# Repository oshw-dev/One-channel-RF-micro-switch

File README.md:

# One-channel-RF-micro-switch
Small one-channel RF microswitch

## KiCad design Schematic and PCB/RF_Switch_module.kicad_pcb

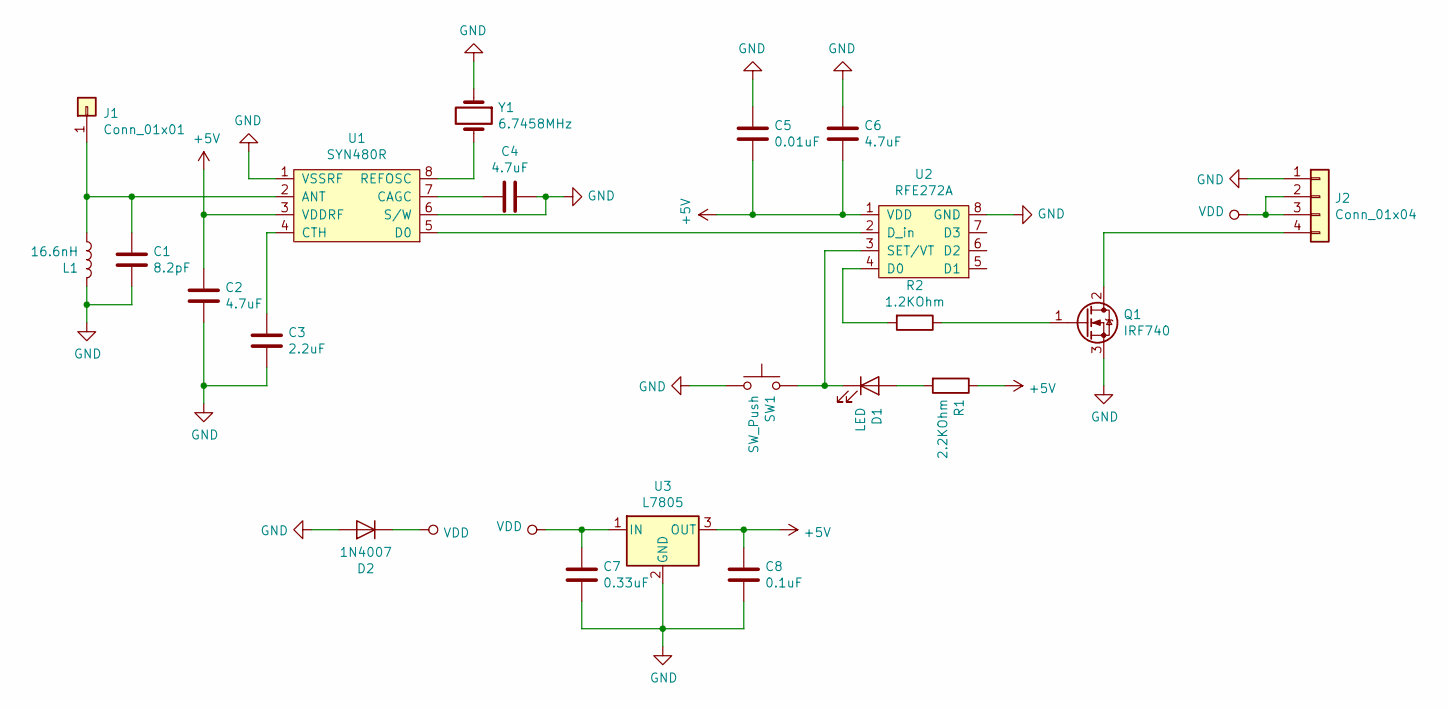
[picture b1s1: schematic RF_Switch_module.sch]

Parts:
C1: 8.2pF; C_0402_1005Metric
C2, C4, C6: 4.7uF; C_0402_1005Metric
C3: 2.2uF; C_0402_1005Metric
C5: 0.01uF; C_0402_1005Metric
C7: 0.33uF; C_0402_1005Metric
C8: 0.1uF; C_0402_1005Metric
D1: LED; LED_0402_1005Metric
D2: 1N4007; D_SOD-123
J1: Conn_01x01; SolderWirePad_1x01_Drill0.8mm
J2: Conn_01x04; PinHeader_1x04_P2.54mm_Horizontal
L1: 16.6nH; L_0402_1005Metric
Q1: IRF740; TO-252-3_TabPin2
R1: 2.2KOhm; R_0402_1005Metric
R2: 1.2KOhm; R_0402_1005Metric
SW1: SW_Push; SW_Push_SPST_NO_Alps_SKRK
U1: SYN480R; SO-8_3.9x4.9mm_P1.27mm
U2: RFE272A; SO-8_3.9x4.9mm_P1.27mm
U3: L7805; SOT-89-3
Y1: 6.7458MHz; Crystal_HC49-U_Vertical

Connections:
+5V: C2.1, C5.2, C6.2, C8.1, R1.1, U1.3 (VDDRF), U2.1 (VDD), U3.3 (OUT)
GND: C1.2, C2.2, C3.2, C4.1, C5.1, C6.1, C7.2, C8.2, D2.2 (A), J2.1, L1.2, Q1.3 (S), SW1.1, U1.1 (VSSRF), U1.6 (S/W), U2.8 (GND), U3.2 (GND), Y1.1
unnamed: C1.1, J1.1, L1.1, U1.2 (ANT)
unnamed: C3.1, U1.4 (CTH)
unnamed: C4.2, U1.7 (CAGC)
unnamed: D1.1 (K), SW1.2, U2.3 (SET/VT)
unnamed: D1.2 (A), R1.2
unnamed: J2.4, Q1.2 (D)
unnamed: Q1.1 (G), R2.1
unnamed: R2.2, U2.4 (D0)
unnamed: U1.5 (D0), U2.2 (D_in)
unnamed: U1.8 (REFOSC), Y1.2
VDD: C7.1, D2.1 (K), J2.2, J2.3, U3.1 (IN)

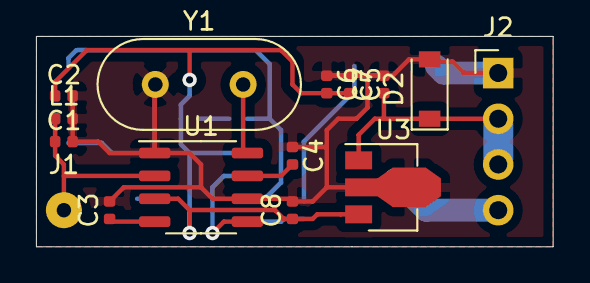
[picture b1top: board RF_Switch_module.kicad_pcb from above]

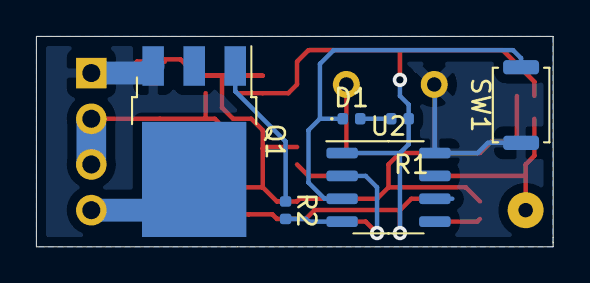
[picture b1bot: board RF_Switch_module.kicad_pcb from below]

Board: 2 copper layers, 28.7 x 11.7 mm, 21 parts (6 on the bottom side), 13 nets.

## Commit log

2019-05-10 Test
2019-05-11 Schematic and PCB
2019-05-11 Pull
2019-05-13 Routing
